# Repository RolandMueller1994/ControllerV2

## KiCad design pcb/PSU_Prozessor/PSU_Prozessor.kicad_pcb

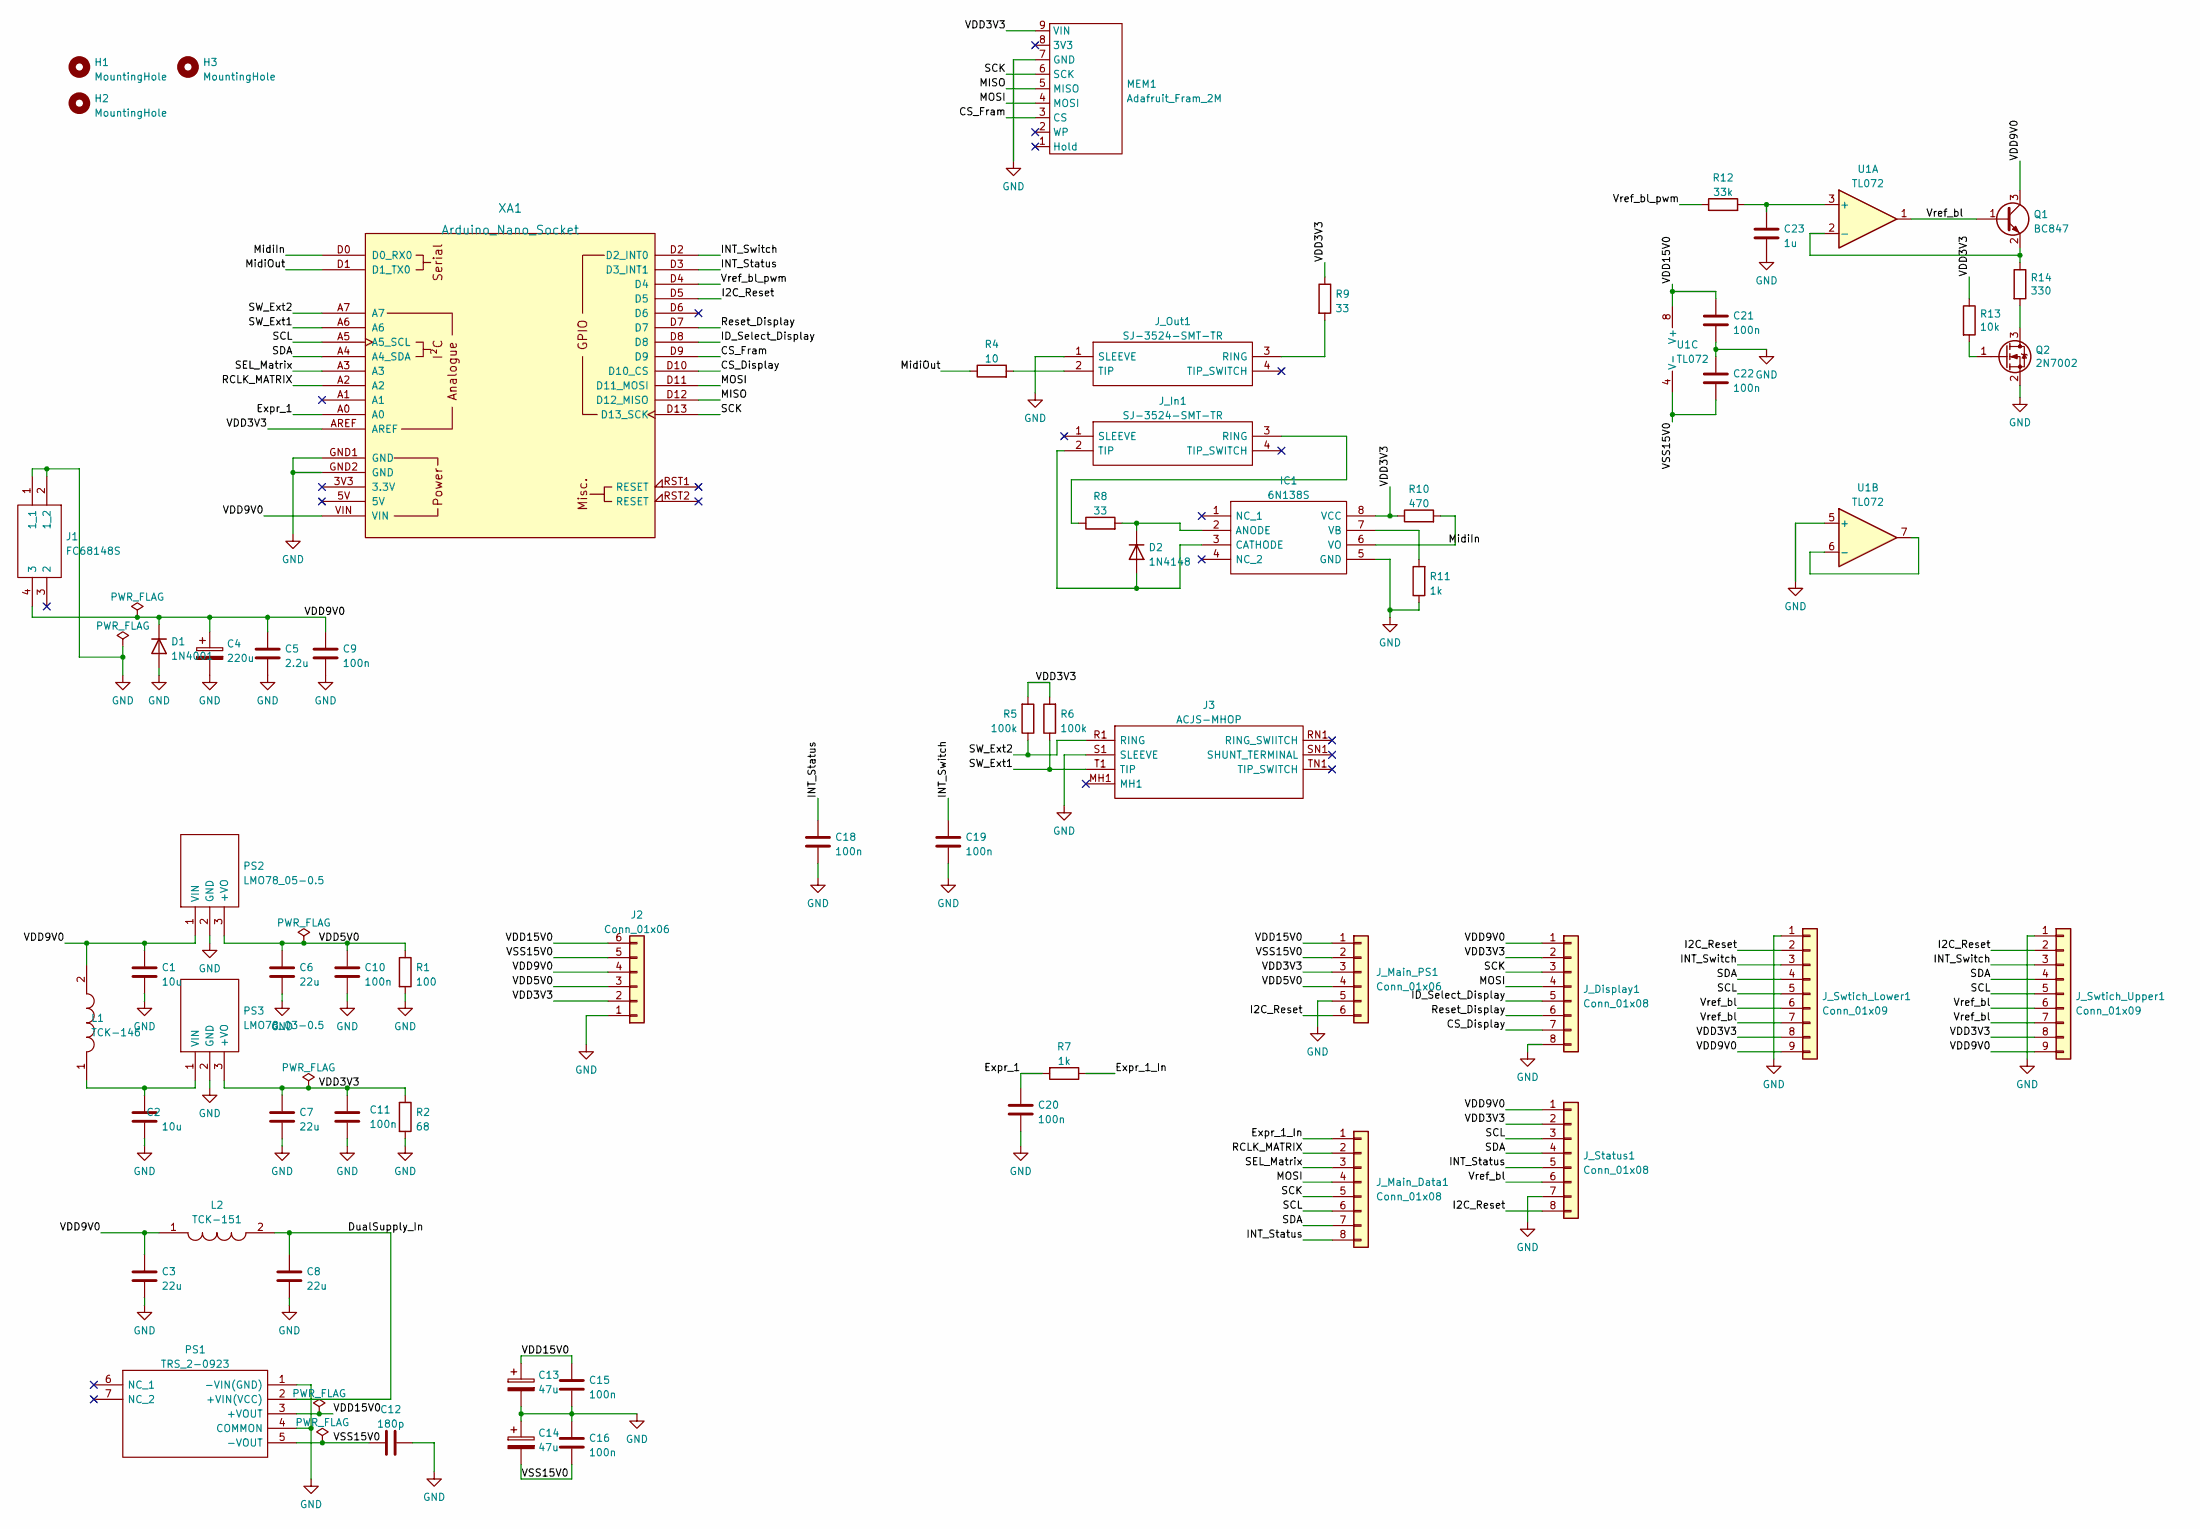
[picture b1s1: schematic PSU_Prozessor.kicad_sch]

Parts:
C1, C2: 10u; C_1206_3216Metric_Pad1.33x1.80mm_HandSolder
C3, C6, C7, C8: 22u; C_1206_3216Metric_Pad1.33x1.80mm_HandSolder
C4: 220u; CP_Elec_10x10
C5: 2.2u; C_1206_3216Metric_Pad1.33x1.80mm_HandSolder
C9, C10, C11, C15, C16, C18, C19, C20, C21, C22: 100n; C_1206_3216Metric_Pad1.33x1.80mm_HandSolder
C12: 180p; C_1206_3216Metric_Pad1.33x1.80mm_HandSolder
C13, C14: 47u; CP_Elec_8x10.5
C23: 1u; C_1206_3216Metric_Pad1.33x1.80mm_HandSolder
D1: 1N4001; D_DO-41_SOD81_P10.16mm_Horizontal
D2: 1N4148; D_SOD-123
H1, H2, H3: MountingHole; MountingHole_4mm
IC1: 6N138S; SOP254P1016X460-8N; Manufacturer_Part_Number 6N138S; Mouser Part Number 859-6N138S
J1: FC68148S; FC68148S_2; Manufacturer_Part_Number FC68148S
J2: Conn_01x06; PinHeader_1x06_P2.54mm_Vertical
J3: ACJS-MHOP; ACJSMHOP; Manufacturer_Part_Number ACJS-MHOP; Mouser Part Number 523-ACJS-MHOP
J_Display1: Conn_01x08; JST_PH_B8B-PH-K_1x08_P2.00mm_Vertical
J_In1: SJ-3524-SMT-TR; Manufacturer_Part_Number SJ-3524-SMT-TR; Mouser Part Number 490-SJ-3524-SMT-TR
J_Main_Data1: Conn_01x08; JST_PH_B8B-PH-K_1x08_P2.00mm_Vertical
J_Main_PS1: Conn_01x06; JST_PH_B6B-PH-K_1x06_P2.00mm_Vertical
J_Out1: SJ-3524-SMT-TR; Manufacturer_Part_Number SJ-3524-SMT-TR; Mouser Part Number 490-SJ-3524-SMT-TR
J_Status1: Conn_01x08; JST_PH_B8B-PH-K_1x08_P2.00mm_Vertical
J_Swtich_Lower1: Conn_01x09; JST_PH_B9B-PH-K_1x09_P2.00mm_Vertical
J_Swtich_Upper1: Conn_01x09; JST_PH_B9B-PH-K_1x09_P2.00mm_Vertical
L1: TCK-146; TCK147; Manufacturer_Part_Number TCK-146; Mouser Part Number 495-TCK-146
L2: TCK-151; TCK151; Manufacturer_Part_Number TCK-151; Mouser Part Number 495-TCK-151
MEM1: Adafruit_Fram_2M; Adafruit_FRam_2M
PS1: TRS_2-0923; TRS20922; Manufacturer_Part_Number TRS 2-0923; Mouser Part Number 495-TRS2-0923
PS2: LMO78_05-0.5; LMO78_0505; Manufacturer_Part_Number LMO78_05-0.5
PS3: LMO78_03-0.5; LMO78_0505; Manufacturer_Part_Number LMO78_05-0.5
Q1: BC847; SOT-23
Q2: 2N7002; SOT-23
R1: 100; R_Axial_DIN0414_L11.9mm_D4.5mm_P15.24mm_Horizontal
R2: 68; R_Axial_DIN0414_L11.9mm_D4.5mm_P15.24mm_Horizontal
R4: 10; R_1206_3216Metric_Pad1.30x1.75mm_HandSolder
R5, R6: 100k; R_1206_3216Metric_Pad1.30x1.75mm_HandSolder
R7, R11: 1k; R_1206_3216Metric_Pad1.30x1.75mm_HandSolder
R8, R9: 33; R_1206_3216Metric_Pad1.30x1.75mm_HandSolder
R10: 470; R_1206_3216Metric_Pad1.30x1.75mm_HandSolder
R12: 33k; R_1206_3216Metric_Pad1.30x1.75mm_HandSolder
R13: 10k; R_1206_3216Metric_Pad1.30x1.75mm_HandSolder
R14: 330; R_1206_3216Metric_Pad1.30x1.75mm_HandSolder
U1: TL072; SOIC127P600X175-8N
XA1: Arduino_Nano_Socket

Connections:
/CS_Display: J_Display1.7, XA1.D10 (D10_CS)
/CS_Fram: MEM1.3 (CS), XA1.D9
/DualSupply_In: C8.1, L2.2, PS1.2 (+VIN(VCC))
/Expr_1: C20.1, R7.2, XA1.A0
/Expr_1_In: J_Main_Data1.1, R7.1
/I2C_Reset: J_Main_PS1.6, J_Status1.8, J_Swtich_Lower1.2, J_Swtich_Upper1.2, XA1.D5
/ID_Select_Display: J_Display1.5, XA1.D8
/INT_Status: C18.1, J_Main_Data1.8, J_Status1.5, XA1.D3 (D3_INT1)
/INT_Switch: C19.1, J_Swtich_Lower1.3, J_Swtich_Upper1.3, XA1.D2 (D2_INT0)
/MISO: MEM1.5 (MISO), XA1.D12 (D12_MISO)
/MOSI: J_Display1.4, J_Main_Data1.4, MEM1.4 (MOSI), XA1.D11 (D11_MOSI)
/MidiIn: IC1.6 (VO), R10.2, XA1.D0 (D0_RX0)
/MidiOut: R4.1, XA1.D1 (D1_TX0)
/RCLK_MATRIX: J_Main_Data1.2, XA1.A2
/Reset_Display: J_Display1.6, XA1.D7
/SCK: J_Display1.3, J_Main_Data1.5, MEM1.6 (SCK), XA1.D13 (D13_SCK)
/SCL: J_Main_Data1.6, J_Status1.3, J_Swtich_Lower1.5, J_Swtich_Upper1.5, XA1.A5 (A5_SCL)
/SDA: J_Main_Data1.7, J_Status1.4, J_Swtich_Lower1.4, J_Swtich_Upper1.4, XA1.A4 (A4_SDA)
/SEL_Matrix: J_Main_Data1.3, XA1.A3
/SW_Ext1: J3.T1 (TIP), R6.1, XA1.A6
/SW_Ext2: J3.R1 (RING), R5.1, XA1.A7
/VDD3V3: C7.1, C11.1, IC1.8 (VCC), J2.2, J_Display1.2, J_Main_PS1.3, J_Status1.2, J_Swtich_Lower1.8, J_Swtich_Upper1.8, MEM1.9 (VIN), PS3.3 (+VO), R2.1, R5.2, R6.2, R9.1, R10.1, R13.1, XA1.AREF
/VDD5V0: C6.1, C10.1, J2.3, J_Main_PS1.4, PS2.3 (+VO), R1.1
/VDD9V0: C1.1, C3.1, C4.1, C5.1, C9.1, D1.1 (K), J1.4 (3), J2.4, J_Display1.1, J_Status1.1, J_Swtich_Lower1.9, J_Swtich_Upper1.9, L1.2, L2.1, PS2.1 (VIN), Q1.3 (C), XA1.VIN
/VDD15V0: C13.1, C15.1, C21.1, J2.6, J_Main_PS1.1, PS1.3 (+VOUT), U1.8 (V+)
/VSS15V0: C12.1, C14.2, C16.2, C22.2, J2.5, J_Main_PS1.2, PS1.5 (-VOUT), U1.4 (V-)
/Vref_bl: J_Status1.6, J_Swtich_Lower1.6, J_Swtich_Lower1.7, J_Swtich_Upper1.6, J_Swtich_Upper1.7, Q1.1 (B), U1.1
/Vref_bl_pwm: R12.1, XA1.D4
GND: C1.2, C2.2, C3.2, C4.2, C5.2, C6.2, C7.2, C8.2, C9.2, C10.2, C11.2, C12.2, C13.2, C14.1, C15.2, C16.1, C18.2, C19.2, C20.2, C21.2, C22.1, C23.2, D1.2 (A), IC1.5 (GND), J1.1 (1_1), J1.2 (1_2), J2.1, J3.S1 (SLEEVE), J_Display1.8, J_Main_PS1.5, J_Out1.1 (SLEEVE), J_Status1.7, J_Swtich_Lower1.1, J_Swtich_Upper1.1, MEM1.7 (GND), PS1.1 (-VIN(GND)), PS1.4 (COMMON), PS2.2 (GND), PS3.2 (GND), Q2.2 (S), R1.2, R2.2, R11.1, U1.5 (+), XA1.GND1 (GND), XA1.GND2 (GND)
unnamed: C2.1, L1.1, PS3.1 (VIN)
unnamed: C23.1, R12.2, U1.3 (+)
unnamed: D2.1 (K), IC1.2 (ANODE), R8.2
unnamed: D2.2 (A), IC1.3 (CATHODE), J_In1.2 (TIP)
unnamed: IC1.7 (VB), R11.2
unnamed: J_In1.3 (RING), R8.1
unnamed: J_Out1.2 (TIP), R4.2
unnamed: J_Out1.3 (RING), R9.2
unnamed: Q1.2 (E), R14.1, U1.2 (-)
unnamed: Q2.1 (G), R13.2
unnamed: Q2.3 (D), R14.2
unnamed: U1.6 (-), U1.7

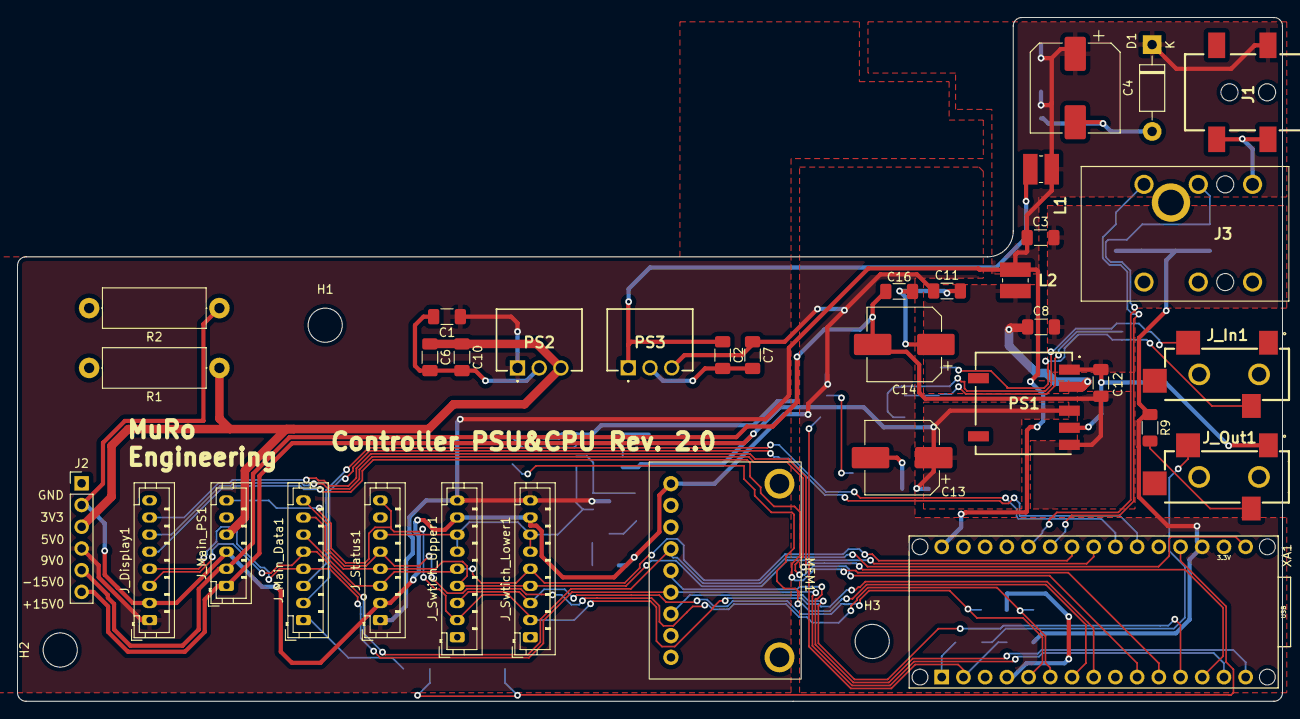
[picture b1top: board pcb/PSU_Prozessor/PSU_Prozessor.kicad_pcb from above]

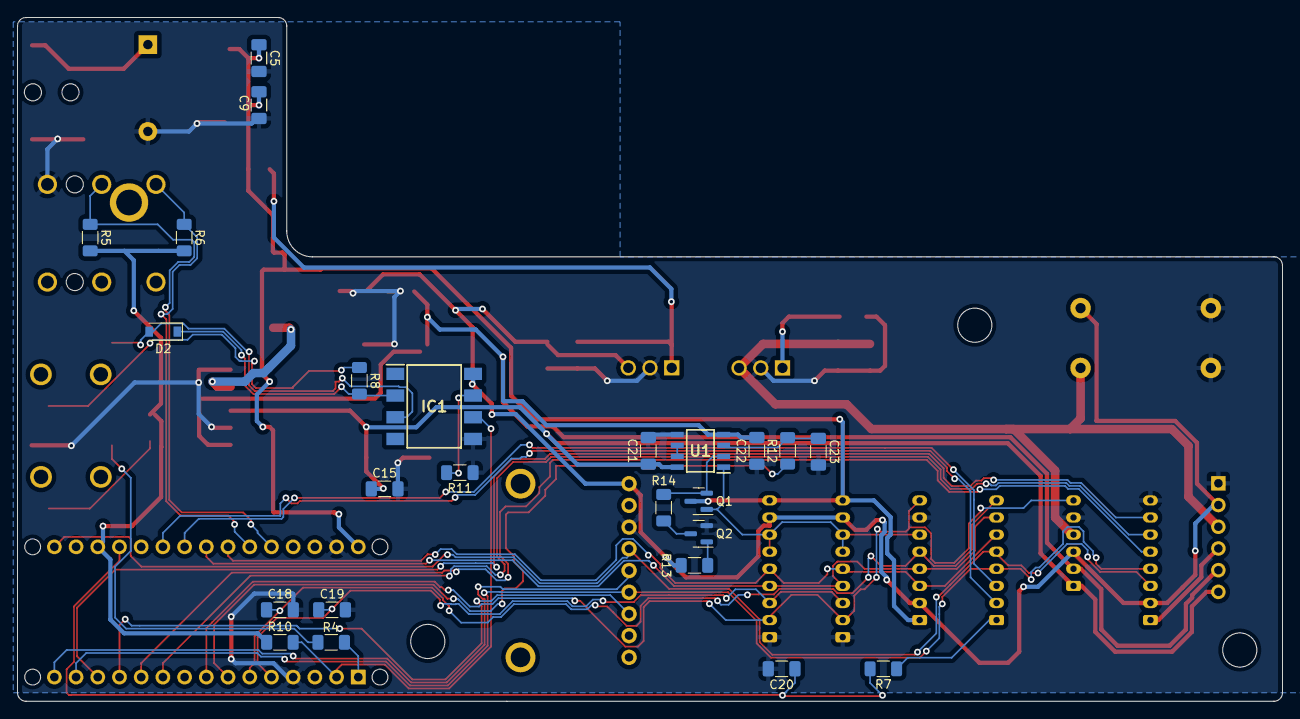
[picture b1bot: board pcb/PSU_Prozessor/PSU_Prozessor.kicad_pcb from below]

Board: 2 copper layers, 148.0 x 80.0 mm, 62 parts (24 on the bottom side), 41 nets.

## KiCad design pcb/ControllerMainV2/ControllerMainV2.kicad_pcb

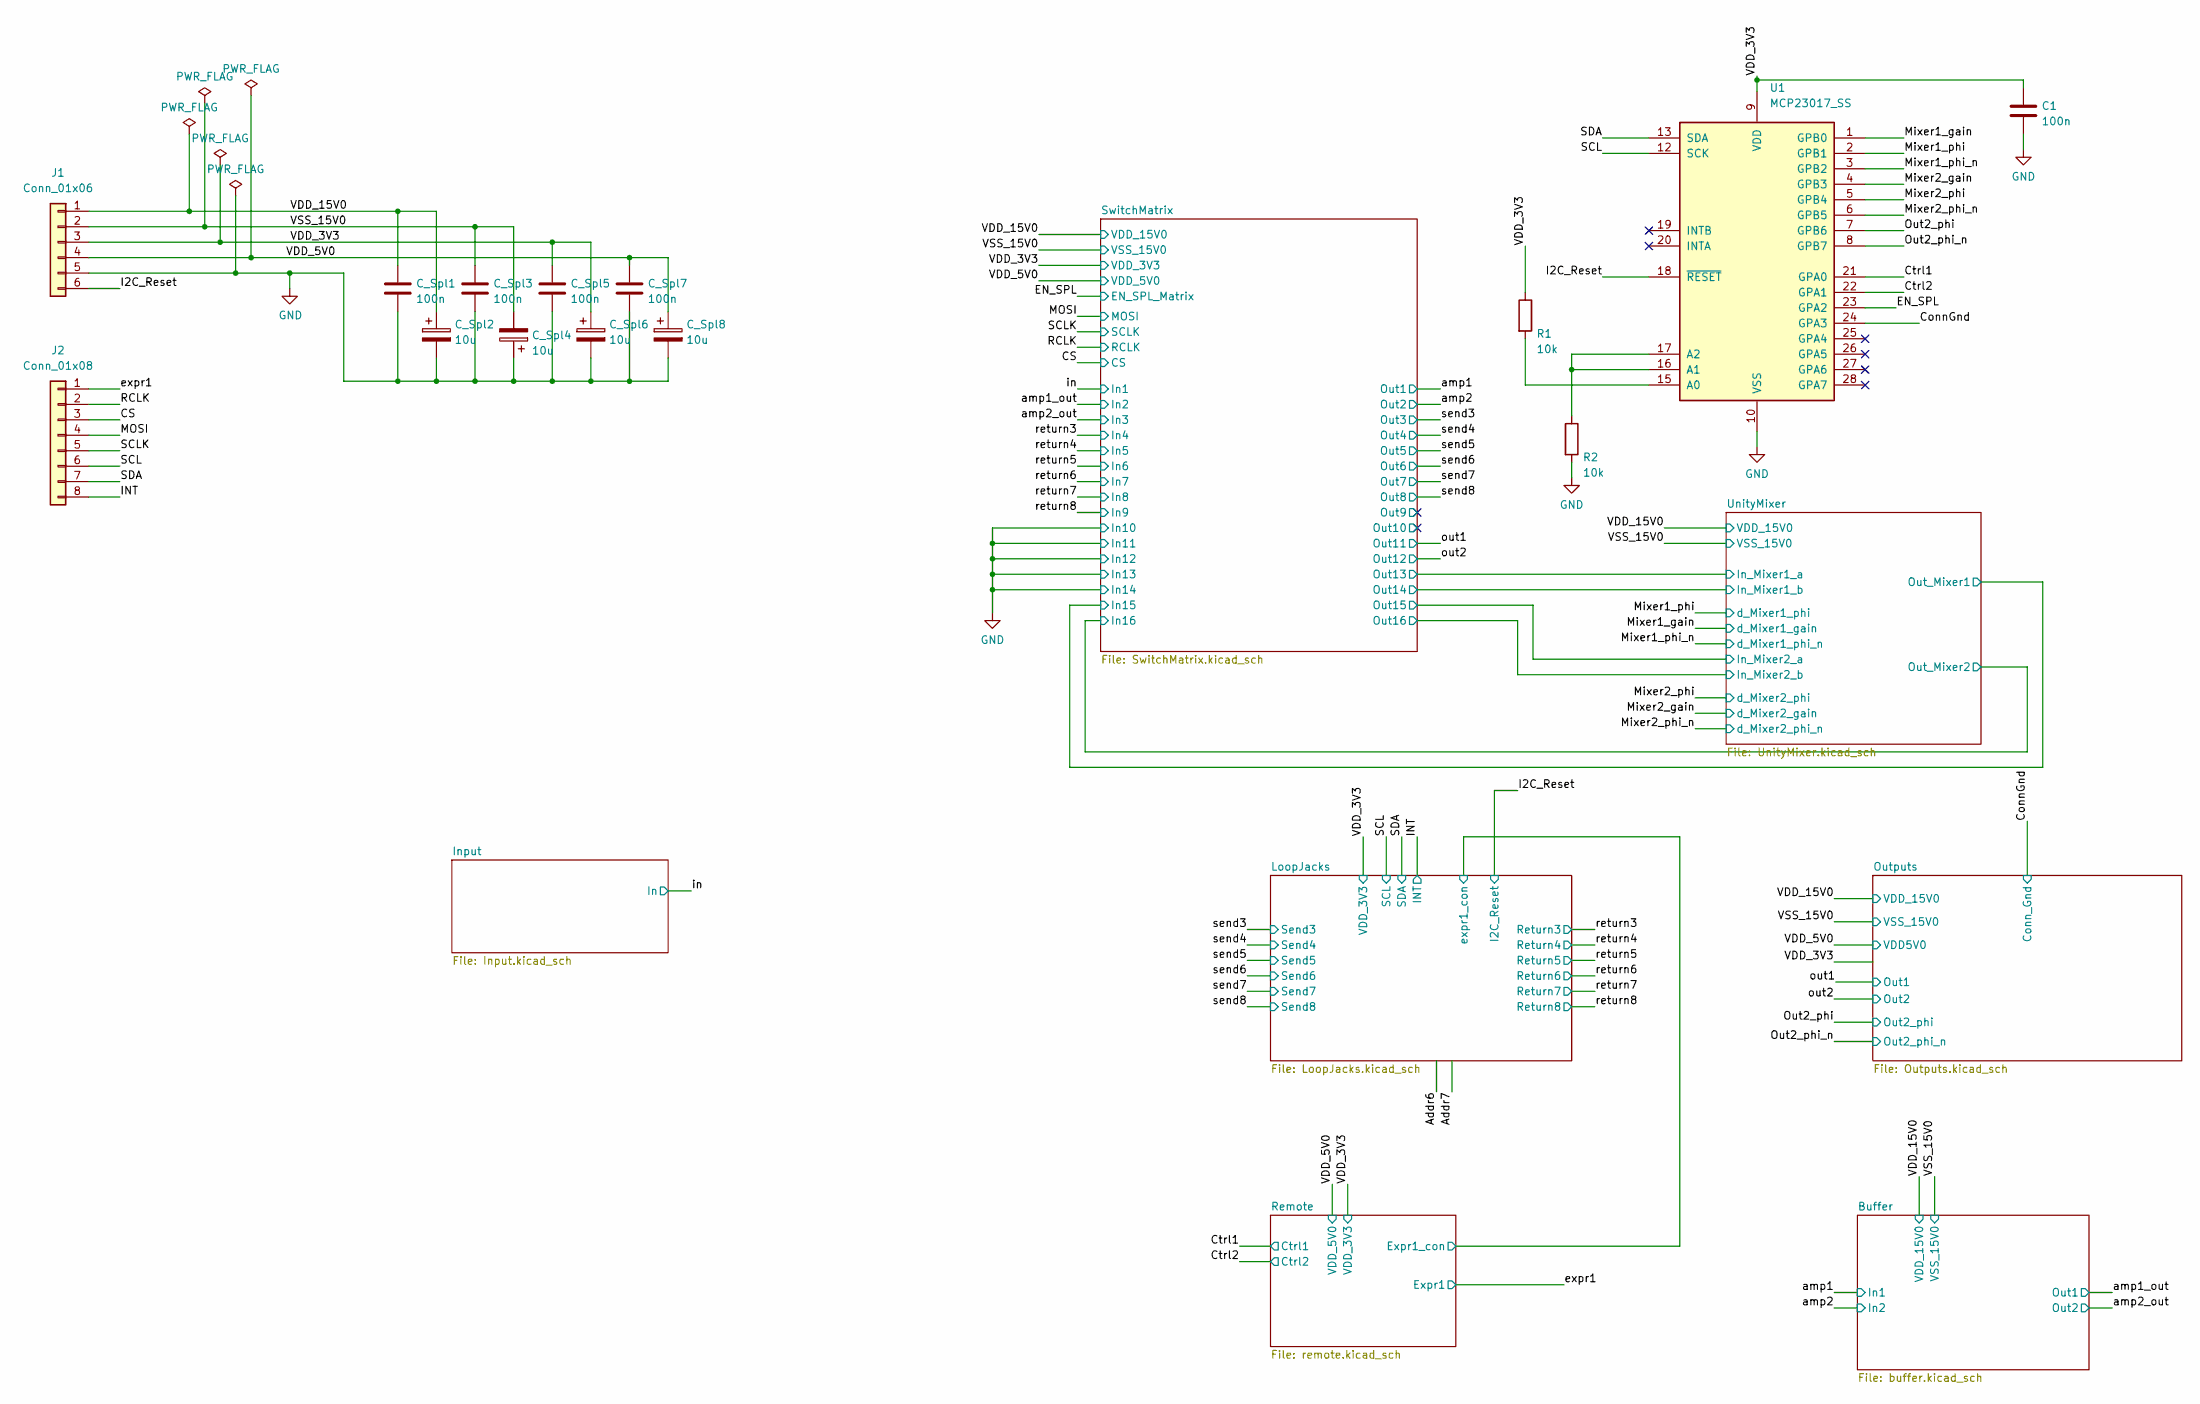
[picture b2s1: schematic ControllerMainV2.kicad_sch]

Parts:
C1: 100n; C_1206_3216Metric_Pad1.33x1.80mm_HandSolder
C_Spl1, C_Spl3, C_Spl5, C_Spl7: 100n; C_1206_3216Metric_Pad1.33x1.80mm_HandSolder
C_Spl2, C_Spl4, C_Spl6, C_Spl8: 10u; C_Elec_4x5.4
J1: Conn_01x06; JST_PH_B6B-PH-K_1x06_P2.00mm_Vertical
J2: Conn_01x08; JST_PH_B8B-PH-K_1x08_P2.00mm_Vertical
R1, R2: 10k; R_0805_2012Metric_Pad1.20x1.40mm_HandSolder
U1: MCP23017_SS; SSOP-28_5.3x10.2mm_P0.65mm

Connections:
/CS: J2.3; also elsewhere on the board
/ConnGnd: U1.24 (GPA3); also elsewhere on the board
/Ctrl1: U1.21 (GPA0); also elsewhere on the board
/Ctrl2: U1.22 (GPA1); also elsewhere on the board
/EN_SPL: U1.23 (GPA2); also elsewhere on the board
/I2C_Reset: J1.6, U1.18 (~RESET); also elsewhere on the board
/INT: J2.8; also elsewhere on the board
/MOSI: J2.4; also elsewhere on the board
/Mixer1_gain: U1.1 (GPB0); also elsewhere on the board
/Mixer1_phi: U1.2 (GPB1); also elsewhere on the board
/Mixer1_phi_n: U1.3 (GPB2); also elsewhere on the board
/Mixer2_gain: U1.4 (GPB3); also elsewhere on the board
/Mixer2_phi: U1.5 (GPB4); also elsewhere on the board
/Mixer2_phi_n: U1.6 (GPB5); also elsewhere on the board
/Out2_phi: U1.7 (GPB6); also elsewhere on the board
/Out2_phi_n: U1.8 (GPB7); also elsewhere on the board
/RCLK: J2.2; also elsewhere on the board
/SCL: J2.6, U1.12 (SCK); also elsewhere on the board
/SCLK: J2.5; also elsewhere on the board
/SDA: J2.7, U1.13 (SDA); also elsewhere on the board
/VDD_3V3: C1.1, C_Spl5.1, C_Spl6.1, J1.3, R1.1, U1.9 (VDD); also elsewhere on the board
/VDD_5V0: C_Spl7.1, C_Spl8.1, J1.4; also elsewhere on the board
/VDD_15V0: C_Spl1.1, C_Spl2.1, J1.1; also elsewhere on the board
/VSS_15V0: C_Spl3.1, C_Spl4.2, J1.2; also elsewhere on the board
/expr1: J2.1; also elsewhere on the board
GND: C1.2, C_Spl1.2, C_Spl2.2, C_Spl3.2, C_Spl4.1, C_Spl5.2, C_Spl6.2, C_Spl7.2, C_Spl8.2, J1.5, R2.2, U1.10 (VSS); also elsewhere on the board
unnamed: R1.2, U1.15 (A0)
unnamed: R2.1, U1.16 (A1), U1.17 (A2)

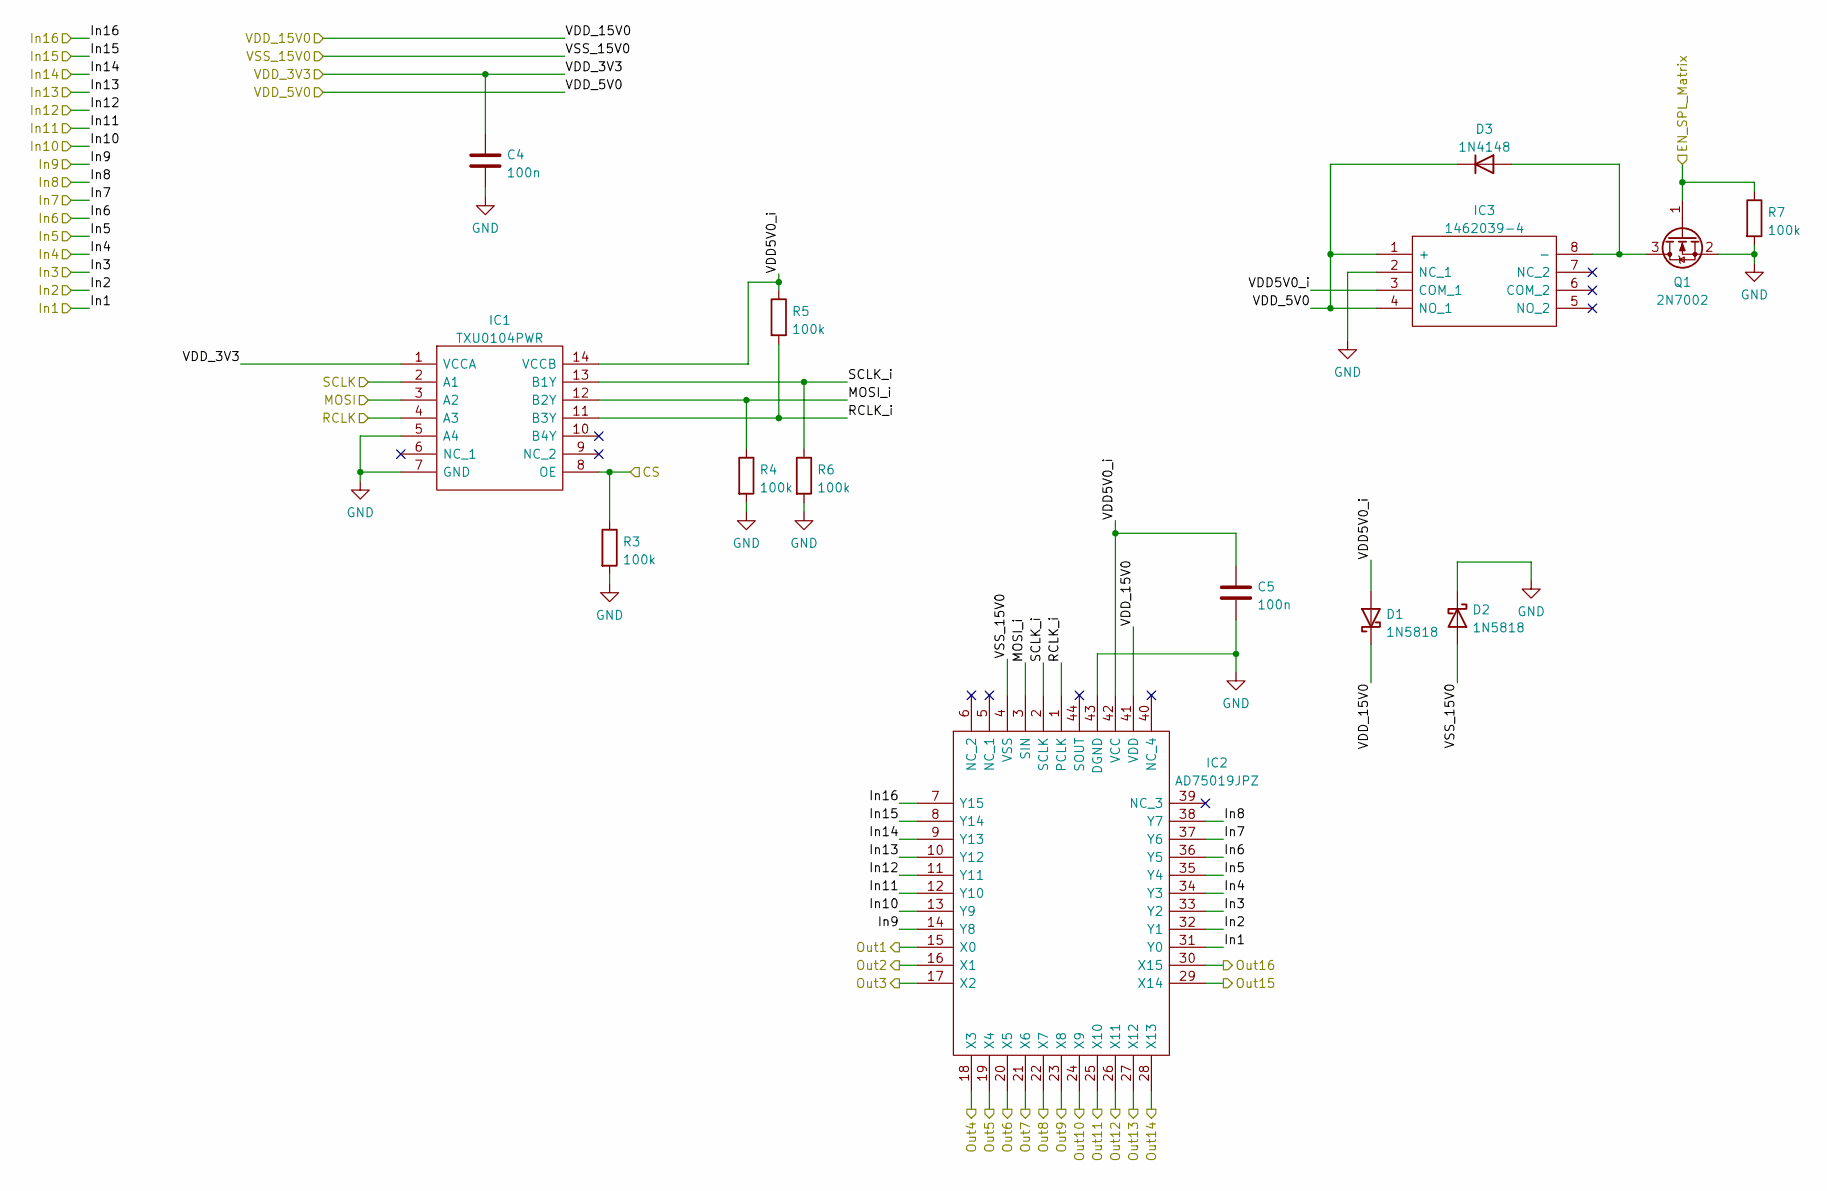
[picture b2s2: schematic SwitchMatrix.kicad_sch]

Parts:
C4, C5: 100n; C_1206_3216Metric_Pad1.33x1.80mm_HandSolder
D1, D2: 1N5818; D_SOD-123
D3: 1N4148; D_SOD-123
IC1: TXU0104PWR; SOP65P640X120-14N; Manufacturer_Part_Number TXU0104PWR; Mouser Part Number 595-TXU0104PWR
IC2: AD75019JPZ; 69802144LF; Manufacturer_Part_Number AD75019JPZ; Mouser Part Number 584-AD75019JPZ
IC3: 1462039-4; 14620394; Manufacturer_Part_Number 1462039-4; Mouser Part Number 655-1462039-4
Q1: 2N7002; SOT-23
R3, R4, R5, R6, R7: 100k; R_0805_2012Metric_Pad1.20x1.40mm_HandSolder

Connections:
/CS: IC1.8 (OE), R3.1; also elsewhere on the board
/EN_SPL: Q1.1 (G), R7.1; also elsewhere on the board
/MOSI: IC1.3 (A2); also elsewhere on the board
/RCLK: IC1.4 (A3); also elsewhere on the board
/SCLK: IC1.2 (A1); also elsewhere on the board
/SwitchMatrix/In15: IC2.8 (Y14); also elsewhere on the board
/SwitchMatrix/In16: IC2.7 (Y15); also elsewhere on the board
/SwitchMatrix/MOSI_i: IC1.12 (B2Y), IC2.3 (SIN), R4.1
/SwitchMatrix/Out9: IC2.23 (X8)
/SwitchMatrix/Out10: IC2.24 (X9)
/SwitchMatrix/Out13: IC2.27 (X12); also elsewhere on the board
/SwitchMatrix/Out14: IC2.28 (X13); also elsewhere on the board
/SwitchMatrix/Out15: IC2.29 (X14); also elsewhere on the board
/SwitchMatrix/Out16: IC2.30 (X15); also elsewhere on the board
/SwitchMatrix/RCLK_i: IC1.11 (B3Y), IC2.1 (PCLK), R5.2
/SwitchMatrix/SCLK_i: IC1.13 (B1Y), IC2.2 (SCLK), R6.1
/SwitchMatrix/VDD5V0_i: C5.1, D1.2 (A), IC1.14 (VCCB), IC2.42 (VCC), IC3.3 (COM_1), R5.1
/VDD_3V3: C4.1, IC1.1 (VCCA); also elsewhere on the board
/VDD_5V0: D3.1 (K), IC3.1 (+), IC3.4 (NO_1); also elsewhere on the board
/VDD_15V0: D1.1 (K), IC2.41 (VDD); also elsewhere on the board
/VSS_15V0: D2.2 (A), IC2.4 (VSS); also elsewhere on the board
/amp1: IC2.15 (X0); also elsewhere on the board
/amp1_out: IC2.32 (Y1); also elsewhere on the board
/amp2: IC2.16 (X1); also elsewhere on the board
/amp2_out: IC2.33 (Y2); also elsewhere on the board
/in: IC2.31 (Y0); also elsewhere on the board
/out1: IC2.25 (X10); also elsewhere on the board
/out2: IC2.26 (X11); also elsewhere on the board
/return3: IC2.34 (Y3); also elsewhere on the board
/return4: IC2.35 (Y4); also elsewhere on the board
/return5: IC2.36 (Y5); also elsewhere on the board
/return6: IC2.37 (Y6); also elsewhere on the board
/return7: IC2.38 (Y7); also elsewhere on the board
/return8: IC2.14 (Y8); also elsewhere on the board
/send3: IC2.17 (X2); also elsewhere on the board
/send4: IC2.18 (X3); also elsewhere on the board
/send5: IC2.19 (X4); also elsewhere on the board
/send6: IC2.20 (X5); also elsewhere on the board
/send7: IC2.21 (X6); also elsewhere on the board
/send8: IC2.22 (X7); also elsewhere on the board
GND: C4.2, C5.2, D2.1 (K), IC1.5 (A4), IC1.7 (GND), IC2.9 (Y13), IC2.10 (Y12), IC2.11 (Y11), IC2.12 (Y10), IC2.13 (Y9), IC2.43 (DGND), IC3.2 (NC_1), Q1.2 (S), R3.2, R4.2, R6.2, R7.2; also elsewhere on the board
unnamed: D3.2 (A), IC3.8 (-), Q1.3 (D)

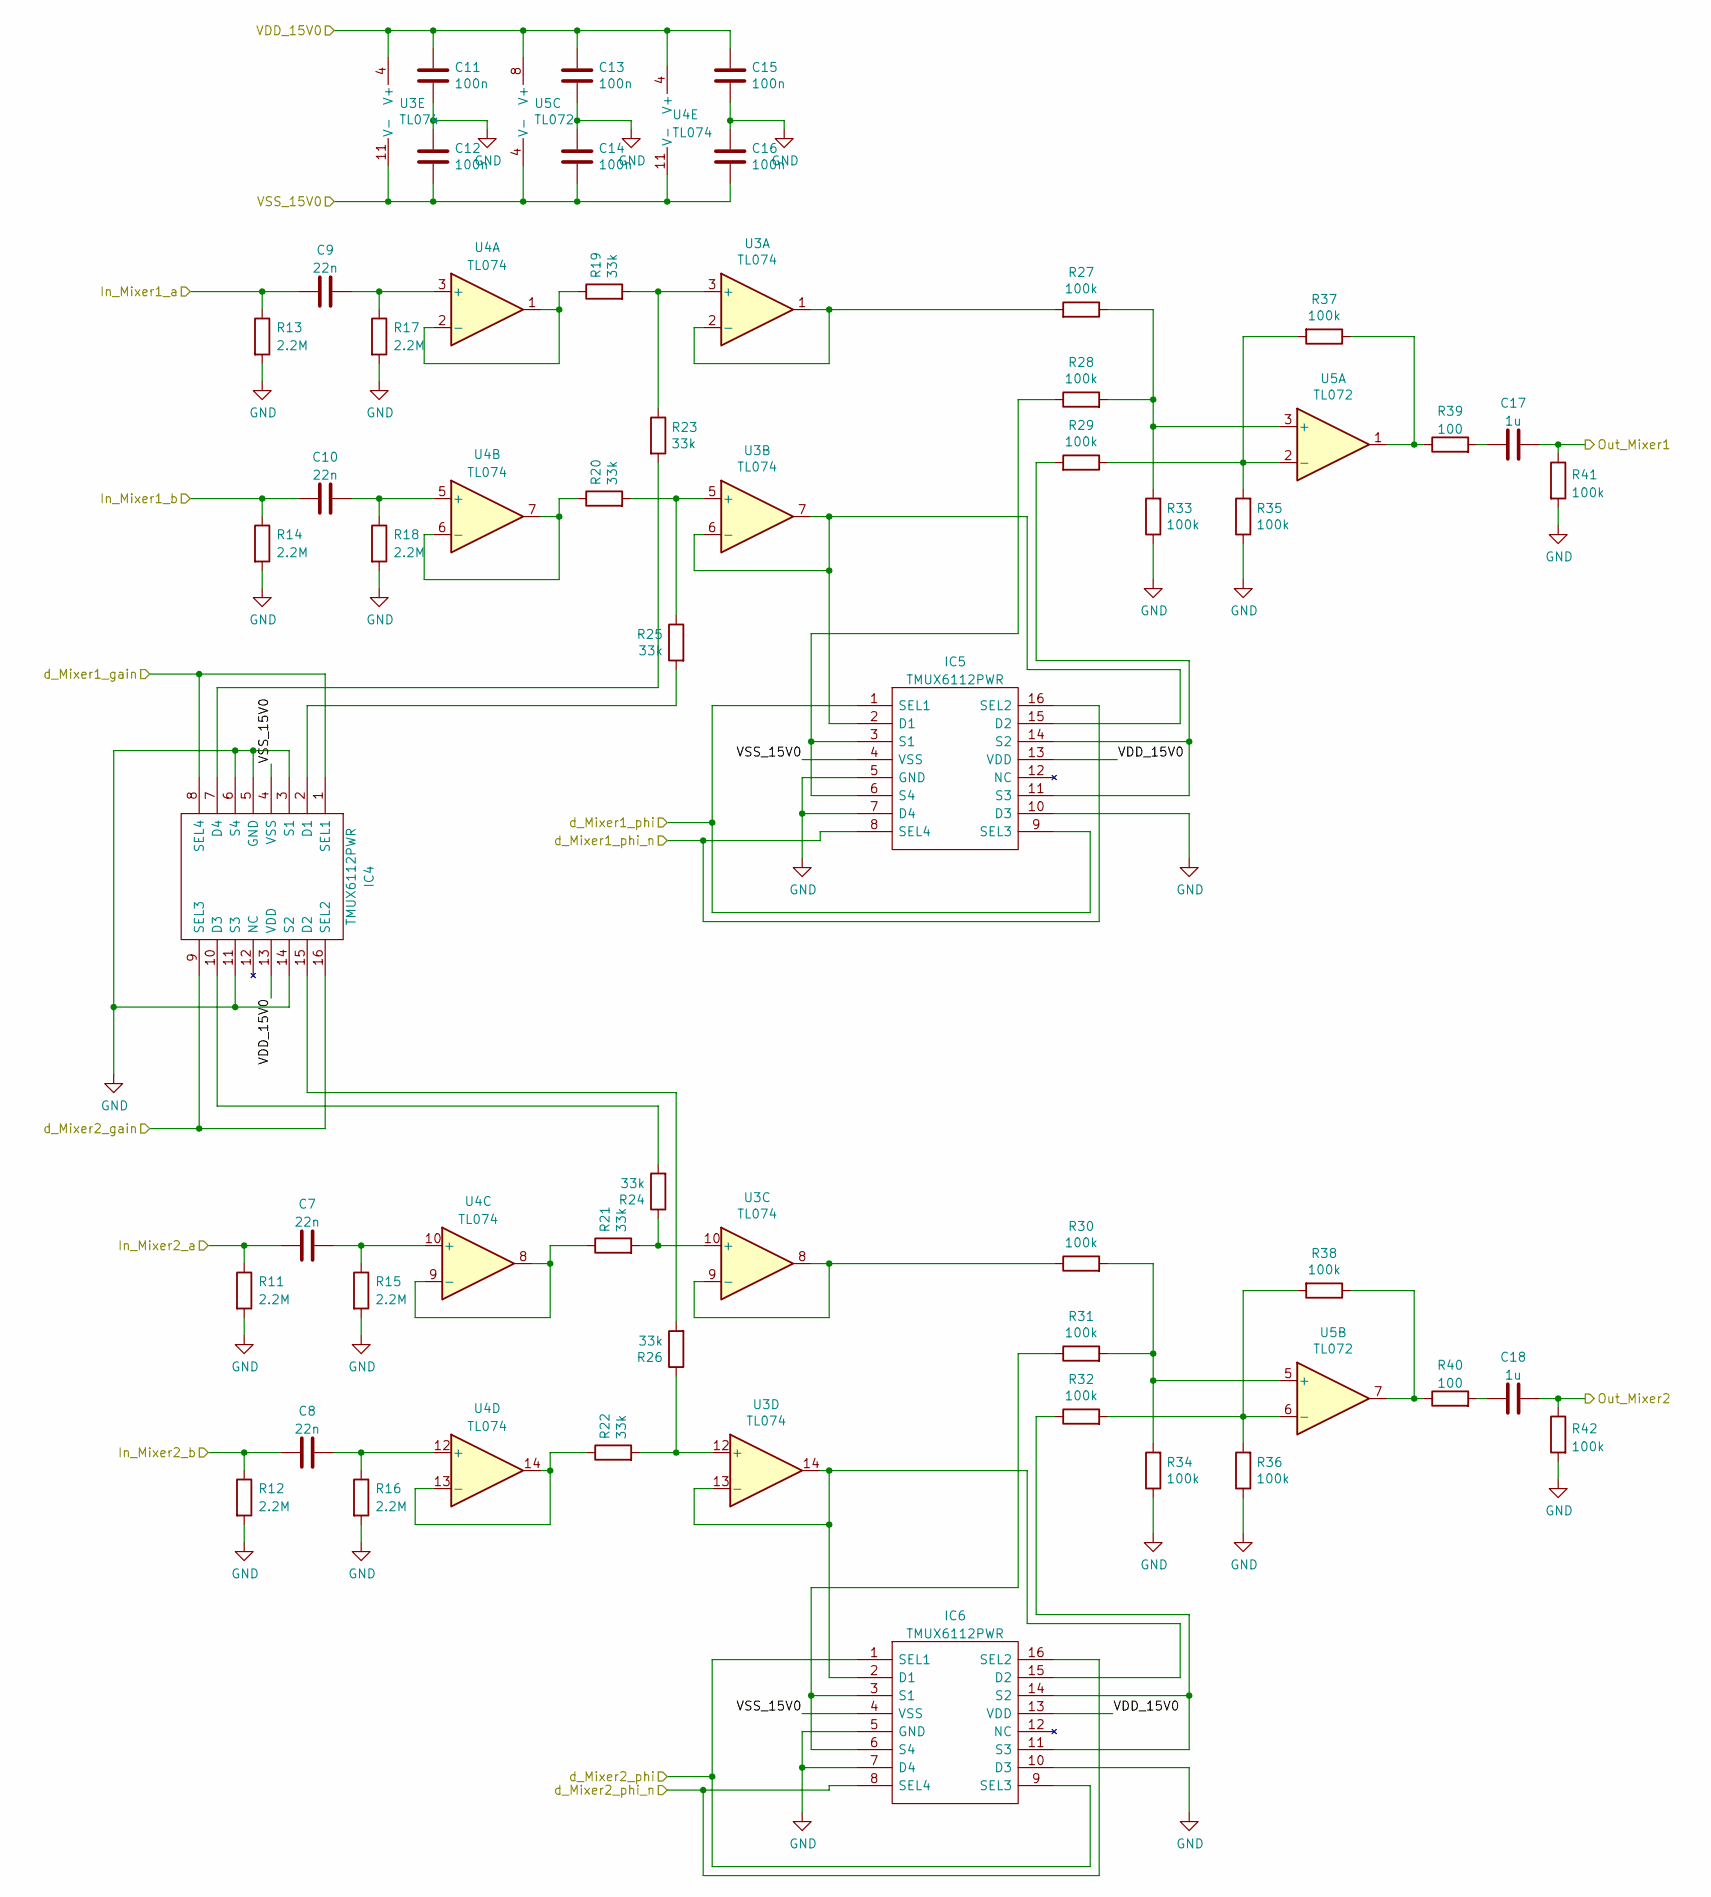
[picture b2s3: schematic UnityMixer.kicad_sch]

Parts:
C7, C8, C9, C10: 22n; C_1206_3216Metric_Pad1.33x1.80mm_HandSolder
C11, C12, C13, C14, C15, C16: 100n; C_1206_3216Metric_Pad1.33x1.80mm_HandSolder
C17, C18: 1u; C_1206_3216Metric_Pad1.33x1.80mm_HandSolder
IC4, IC5, IC6: TMUX6112PWR; SOP65P640X120-16N; Manufacturer_Part_Number TMUX6112PWR; Mouser Part Number 595-TMUX6112PWR
R11, R12, R13, R14, R15, R16, R17, R18: 2.2M; R_0805_2012Metric_Pad1.20x1.40mm_HandSolder
R19, R20, R21, R22, R23, R24, R25, R26: 33k; R_0805_2012Metric_Pad1.20x1.40mm_HandSolder
R27, R28, R29, R30, R31, R32, R33, R34, R35, R36, R37, R38, R41, R42: 100k; R_0805_2012Metric_Pad1.20x1.40mm_HandSolder
R39, R40: 100; R_0805_2012Metric_Pad1.20x1.40mm_HandSolder
U3, U4: TL074; SOIC127P600X175-14N
U5: TL072; SOIC-8_3.9x4.9mm_P1.27mm

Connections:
/Mixer1_gain: IC4.1 (SEL1), IC4.8 (SEL4); also elsewhere on the board
/Mixer1_phi: IC5.1 (SEL1), IC5.9 (SEL3); also elsewhere on the board
/Mixer1_phi_n: IC5.8 (SEL4), IC5.16 (SEL2); also elsewhere on the board
/Mixer2_gain: IC4.9 (SEL3), IC4.16 (SEL2); also elsewhere on the board
/Mixer2_phi: IC6.1 (SEL1), IC6.9 (SEL3); also elsewhere on the board
/Mixer2_phi_n: IC6.8 (SEL4), IC6.16 (SEL2); also elsewhere on the board
/SwitchMatrix/In15: C17.2, R41.1; also elsewhere on the board
/SwitchMatrix/In16: C18.2, R42.1; also elsewhere on the board
/SwitchMatrix/Out13: C9.1, R13.1; also elsewhere on the board
/SwitchMatrix/Out14: C10.1, R14.1; also elsewhere on the board
/SwitchMatrix/Out15: C7.1, R11.1; also elsewhere on the board
/SwitchMatrix/Out16: C8.1, R12.1; also elsewhere on the board
/VDD_15V0: C11.1, C13.1, C15.1, IC4.13 (VDD), IC5.13 (VDD), IC6.13 (VDD), U3.4 (V+), U4.4 (V+), U5.8 (V+); also elsewhere on the board
/VSS_15V0: C12.2, C14.2, C16.2, IC4.4 (VSS), IC5.4 (VSS), IC6.4 (VSS), U3.11 (V-), U4.11 (V-), U5.4 (V-); also elsewhere on the board
GND: C11.2, C12.1, C13.2, C14.1, C15.2, C16.1, IC4.3 (S1), IC4.5 (GND), IC4.6 (S4), IC4.11 (S3), IC4.14 (S2), IC5.5 (GND), IC5.7 (D4), IC5.10 (D3), IC6.5 (GND), IC6.7 (D4), IC6.10 (D3), R11.2, R12.2, R13.2, R14.2, R15.2, R16.2, R17.2, R18.2, R33.1, R34.1, R35.1, R36.1, R41.2, R42.2; also elsewhere on the board
unnamed: C7.2, R15.1, U4.10 (+)
unnamed: C8.2, R16.1, U4.12 (+)
unnamed: C9.2, R17.1, U4.3 (+)
unnamed: C10.2, R18.1, U4.5 (+)
unnamed: C17.1, R39.2
unnamed: C18.1, R40.2
unnamed: IC4.2 (D1), R25.2
unnamed: IC4.7 (D4), R23.2
unnamed: IC4.10 (D3), R24.2
unnamed: IC4.15 (D2), R26.2
unnamed: IC5.3 (S1), IC5.6 (S4), R28.1
unnamed: IC5.11 (S3), IC5.14 (S2), R29.2
unnamed: IC5.2 (D1), IC5.15 (D2), U3.6 (-), U3.7
unnamed: IC6.3 (S1), IC6.6 (S4), R31.1
unnamed: IC6.11 (S3), IC6.14 (S2), R32.1
unnamed: IC6.2 (D1), IC6.15 (D2), U3.13 (-), U3.14
unnamed: R19.1, U4.1, U4.2 (-)
unnamed: R19.2, R23.1, U3.3 (+)
unnamed: R20.1, U4.6 (-), U4.7
unnamed: R20.2, R25.1, U3.5 (+)
unnamed: R21.1, U4.8, U4.9 (-)
unnamed: R21.2, R24.1, U3.10 (+)
unnamed: R22.1, U4.13 (-), U4.14
unnamed: R22.2, R26.1, U3.12 (+)
unnamed: R27.1, R28.2, R33.2, U5.3 (+)
unnamed: R27.2, U3.1, U3.2 (-)
unnamed: R29.1, R35.2, R37.2, U5.2 (-)
unnamed: R30.1, U3.8, U3.9 (-)
unnamed: R30.2, R31.2, R34.2, U5.5 (+)
unnamed: R32.2, R36.2, R38.2, U5.6 (-)
unnamed: R37.1, R39.1, U5.1
unnamed: R38.1, R40.1, U5.7
